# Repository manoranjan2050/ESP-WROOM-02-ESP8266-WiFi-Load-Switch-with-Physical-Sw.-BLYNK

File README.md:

# ESP-WROOM-02-ESP8266-WiFi-Load-Switch-with-Physical-Sw.-BLYNK
ESP8266 WiFi Mobile On-Off with Sync. Physical Sw. BLYNK App.

ESP-WROOM-02 BLYNK ONE Switch is a WiFi Load switch for Light Bulb, Fan, A/C etc. 
Synchronized Physical switch change button state on BLYNK server.

For instructions and setup. http://esp8266.signal.com.tr/

for PCB and PCBA Production https://www.pcbway.com/

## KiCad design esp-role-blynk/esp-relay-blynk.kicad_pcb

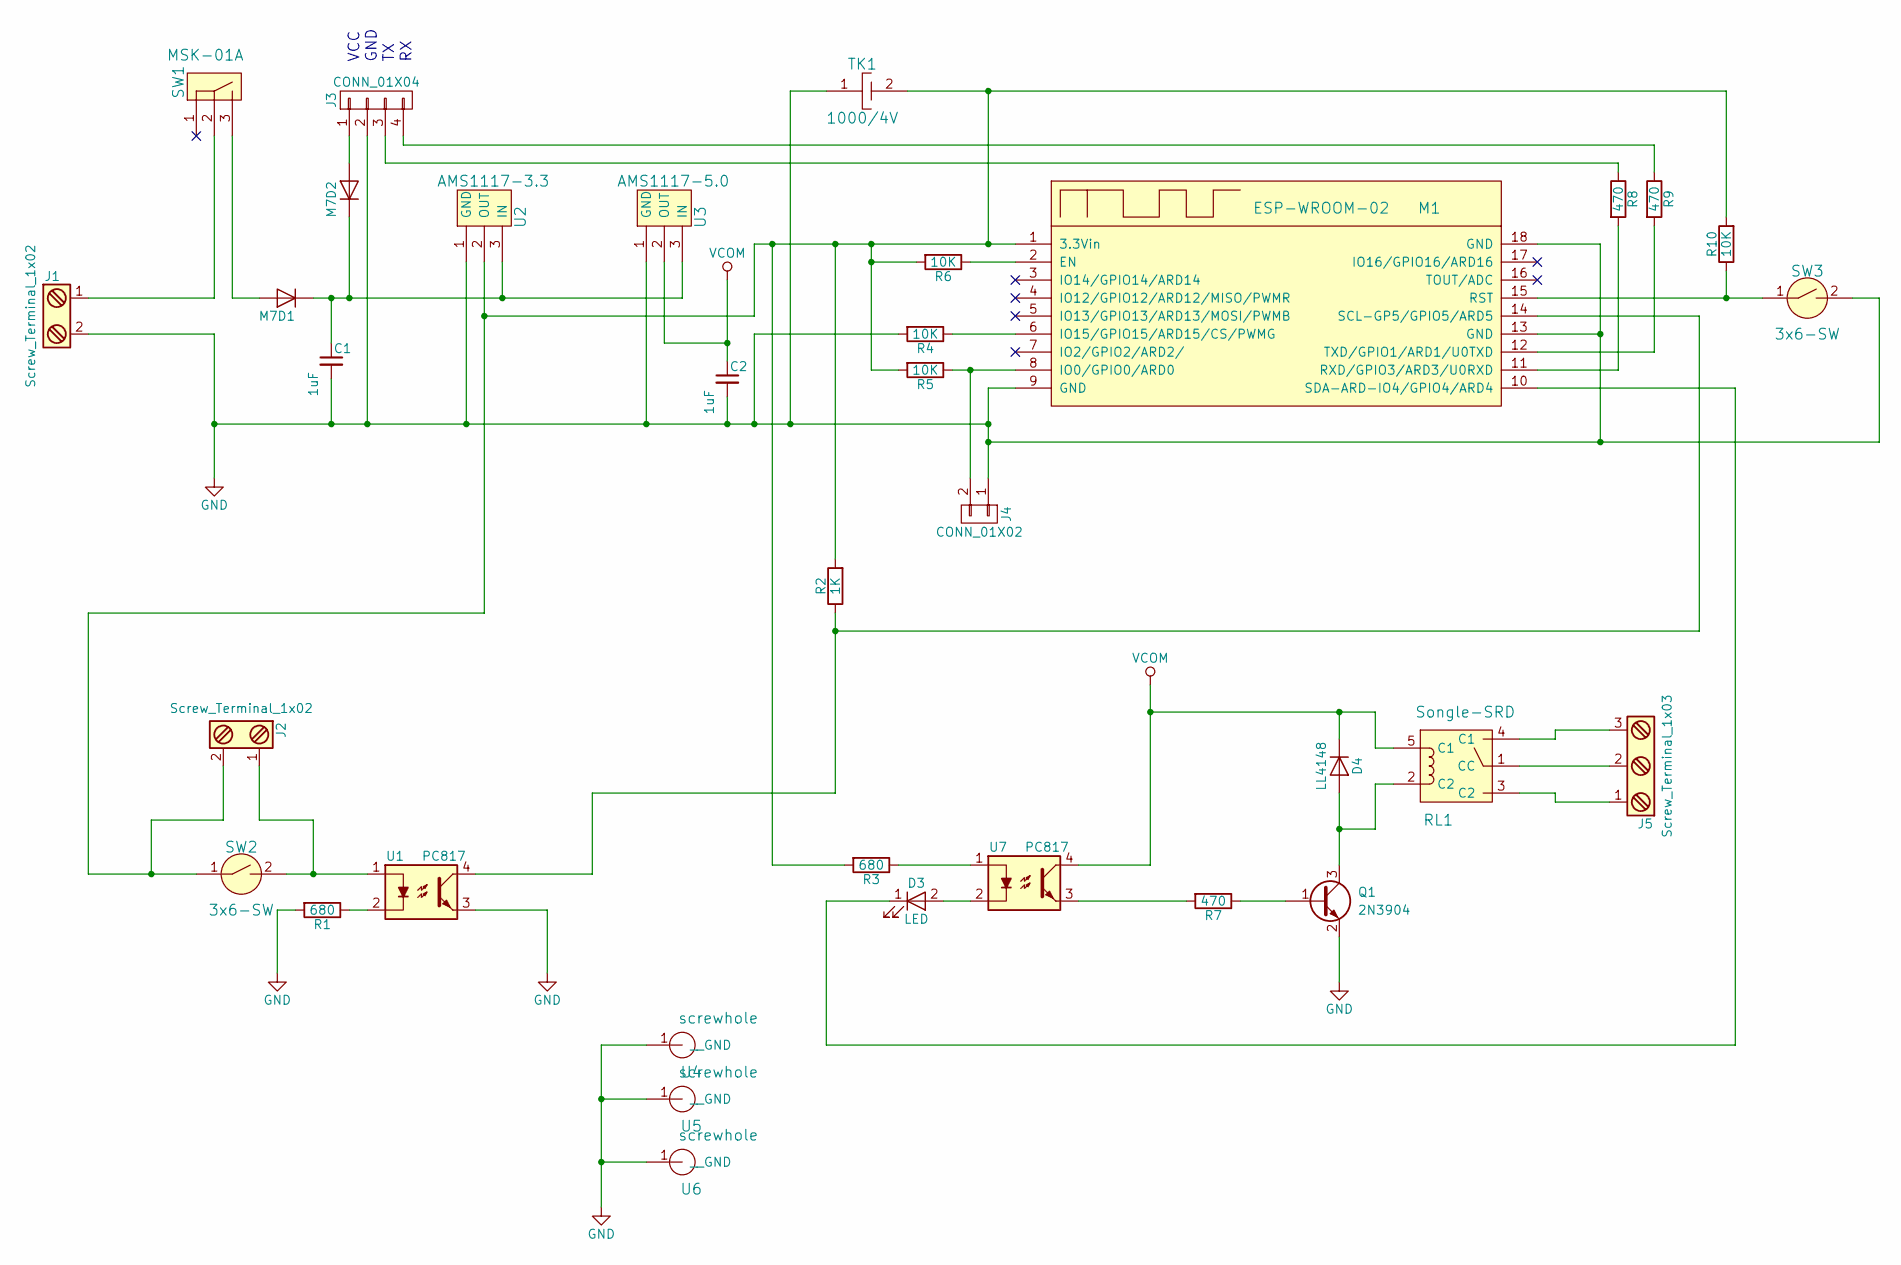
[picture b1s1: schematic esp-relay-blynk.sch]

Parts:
C1, C2: 1uF; C_0805_HandSoldering
D1, D2: M7; D_SMA
D3: LED; LED_0805_HandSoldering
D4: LL4148; D_MiniMELF
J1, J2: Screw_Terminal_1x02; TerminalBlock_Pheonix_PT-3.5mm_2pol
J3: CONN_01X04; Pin_Header_Straight_1x04_Pitch2.54mm
J4: CONN_01X02; Pin_Header_Straight_1x02_Pitch2.54mm
J5: Screw_Terminal_1x03; TerminalBlock_Pheonix_PT-3.5mm_3pol
M1: ESP-WROOM-02
Q1: 2N3904; SOT23HS
R1, R3: 680; R0805HS
R2: 1K; R0805HS
R4, R5, R6, R10: 10K; R0805HS
R7, R8, R9: 470; R0805HS
RL1: Songle-SRD
SW1: MSK-01A
SW2, SW3: 3x6-SW
TK1: 1000/4V; D-CASE-TK
U1, U7: PC817; DIP-4_W7.62mm
U2: AMS1117-3.3; SOT-223
U3: AMS1117-5.0; SOT-223
U4, U5, U6: screwhole; Screwhole

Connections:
GND: C1.2, C2.2, J1.2, J3.2, J4.1, M1.9 (GND), M1.13 (GND), M1.18 (GND), Q1.2 (E), R1.2, R4.2, SW3.2, TK1.1, U1.3, U2.1 (GND), U3.1 (GND), U4.1, U5.1, U6.1
unnamed: C1.1, D1.1 (K), D2.1 (K), U2.3 (IN), U3.3 (IN)
unnamed: D1.2 (A), SW1.3
unnamed: D2.2 (A), J3.1
unnamed: D3.1 (K), M1.10 (SDA-ARD-IO4/GPIO4/ARD4)
unnamed: D3.2 (A), U7.2
unnamed: D4.2 (A), Q1.3 (C), RL1.2 (C2)
unnamed: J1.1, SW1.2
unnamed: J2.1, SW2.2, U1.1
unnamed: J2.2, M1.1 (3.3Vin), R2.2, R3.2, R5.2, R6.2, R10.2, SW2.1, TK1.2, U2.2 (OUT)
unnamed: J3.3, R8.1
unnamed: J3.4, R9.1
unnamed: J4.2, M1.8 (IO0/GPIO0/ARD0), R5.1
unnamed: J5.1, RL1.3 (C2)
unnamed: J5.2, RL1.1 (CC)
unnamed: J5.3, RL1.4 (C1)
unnamed: M1.2 (EN), R6.1
unnamed: M1.6 (IO15/GPIO15/ARD15/CS/PWMG), R4.1
unnamed: M1.11 (RXD/GPIO3/ARD3/U0RXD), R8.2
unnamed: M1.12 (TXD/GPIO1/ARD1/U0TXD), R9.2
unnamed: M1.14 (SCL-GP5/GPIO5/ARD5), R2.1, U1.4
unnamed: M1.15 (RST), R10.1, SW3.1
unnamed: Q1.1 (B), R7.1
unnamed: R1.1, U1.2
unnamed: R3.1, U7.1
unnamed: R7.2, U7.3
VCOM: C2.1, D4.1 (K), RL1.5 (C1), U3.2 (OUT), U7.4

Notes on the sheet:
VCC GND TX RX

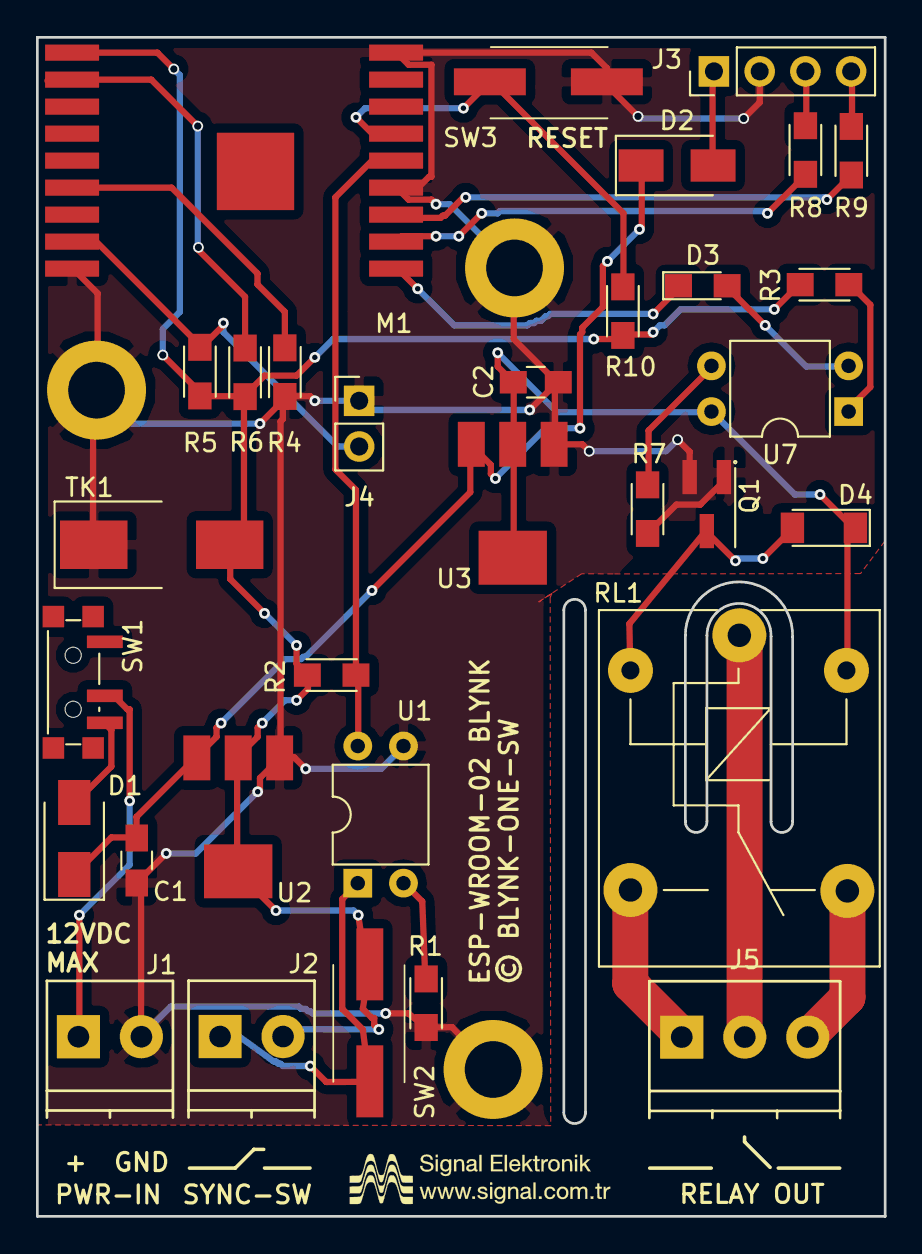
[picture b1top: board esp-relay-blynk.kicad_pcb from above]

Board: 2 copper layers, 47.1 x 65.5 mm, 35 parts (0 on the bottom side), 27 nets.

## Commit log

2017-10-30 PDF Schematics
    PDF Schematics added
2017-10-30 Create Gerber
2017-10-30 ESP-WROOM-02-ESP8266-WiFi-Load-Switch-with-Physical-Sw.-BLYNK
    Files
2017-10-30 ESP-WROOM-02-ESP8266-WiFi-Load-Switch-with-Physical-Sw.-BLYNK
    Push

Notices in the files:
esp-role-blynk/esp-relay-blynk.kicad_pcb:
© BLYNK-ONE-SW
